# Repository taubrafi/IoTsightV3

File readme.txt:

IoTSights Project:
	
	Case --Solidworks files for enclosure

	CC3200_workspace
		{Lots of files}	--	Lots of test/old stuff
		ProjectV3 		-- 	main project files
			ADXL345		--Code for accelerometer (interrupt never implemented)
			DS2401		--Code for hardware ID chip
			GPS			--Turn GPS on and off
			HMC5883		--Code for compass (with callibration)
			IMU			--Math to calculate orientation angles
			main		--main
			MPL115A2	--Code to read form barometer and convers to kPa
			NetworkFunctions	--HTTP/Server functions
			NMEA				--Code to decode the GPS information
			parameters			--a few defines and paramaters
			pinmux2 (pinmux ignored)	--pin setup
			SD_card						--Code to write to SD card (not implemented fully)
			SimpleLinkFunctions			--Code to connect to Wi-Fi network 

	OLD project files 	-- report/presentation documentation
		
	PCB					-- PCB files (eagle)
	
	IoT_Sight_FULL 		-- Full schematic for PCB (pdf)

To get up and running:
	Install the latest version of CCS according to the TI website for the CC3200.
	Install Uniflash CC3200_sdk and servicepack (all folowing TI directions exactly)
	See:		https://www.youtube.com/watch?v=xbh9I8waq5g
	Or search: 	"SimpleLink Wi-Fi CC3200 Project 0: Code Composer Studio IDE"

You're ready to go

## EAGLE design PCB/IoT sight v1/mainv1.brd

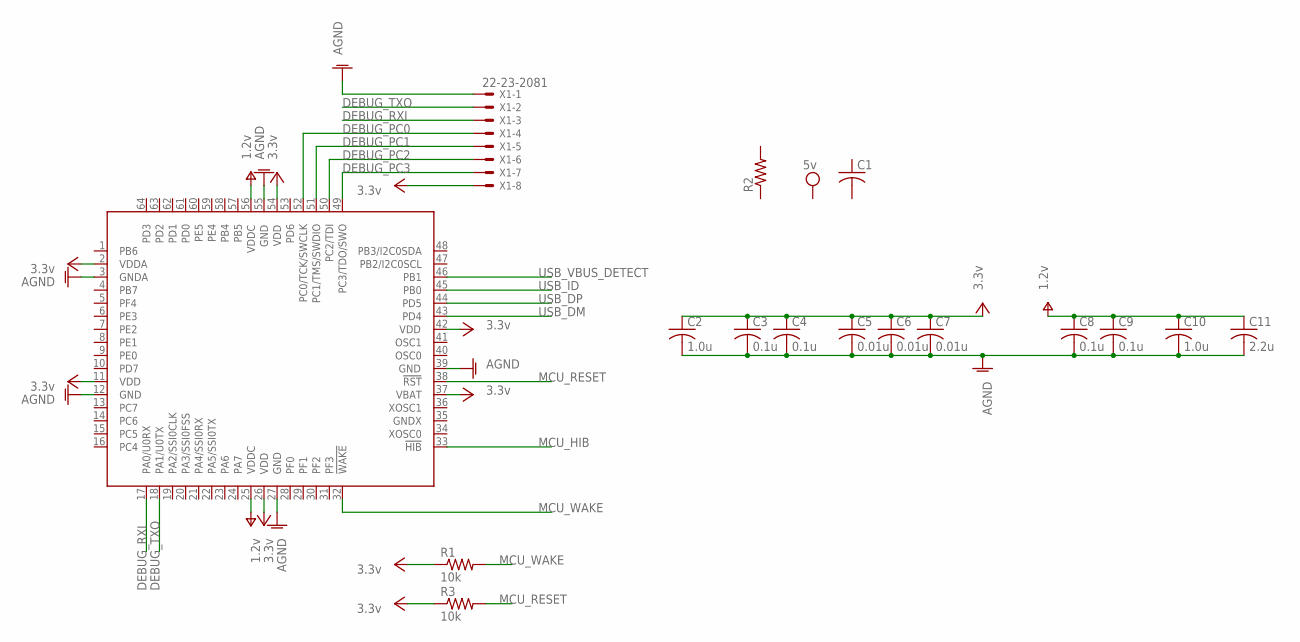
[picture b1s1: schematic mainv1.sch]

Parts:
C1: C-USC0805K; C0805K
C2, C10: 1.0u; C0805K
C3, C4, C8, C9: 0.1u; C0805K
C5, C6, C7: 0.01u; C0805K
C11: 2.2u; C0805K
IC1: TM4C123GH6PMI; PM_S-PQFP-G64
R1, R3: 10k; R0805
R2: R-US_R0805; R0805
X1: 22-23-2081

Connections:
AGND: C2.2, C3.2, C4.2, C5.2, C6.2, C7.2, C8.2, C9.2, C10.2, C11.2, IC1.3 (GNDA), IC1.12 (GND), IC1.27 (GND), IC1.39 (GND), IC1.55 (GND), X1.1
DEBUG_PC0: IC1.52 (PC0/TCK/SWCLK), X1.4
DEBUG_PC1: IC1.51 (PC1/TMS/SWDIO), X1.5
DEBUG_PC2: IC1.50 (PC2/TDI), X1.6
DEBUG_PC3: IC1.49 (PC3/TDO/SWO), X1.7
DEBUG_RXI: IC1.17 (PA0/U0RX), X1.3
DEBUG_TXO: IC1.18 (PA1/U0TX), X1.2
MCU_HIB: IC1.33 (!HIB)
MCU_RESET: IC1.38 (!RST), R3.2
MCU_WAKE: IC1.32 (!WAKE), R1.2
USB_DM: IC1.43 (PD4)
USB_DP: IC1.44 (PD5)
USB_ID: IC1.45 (PB0)
USB_VBUS_DETECT: IC1.46 (PB1)
V+: C8.1, C9.1, C10.1, C11.1, IC1.25 (VDDC), IC1.56 (VDDC)
VCC: C2.1, C3.1, C4.1, C5.1, C6.1, C7.1, IC1.2 (VDDA), IC1.11 (VDD), IC1.26 (VDD), IC1.37 (VBAT), IC1.42 (VDD), IC1.54 (VDD), R1.1, R3.1, X1.8

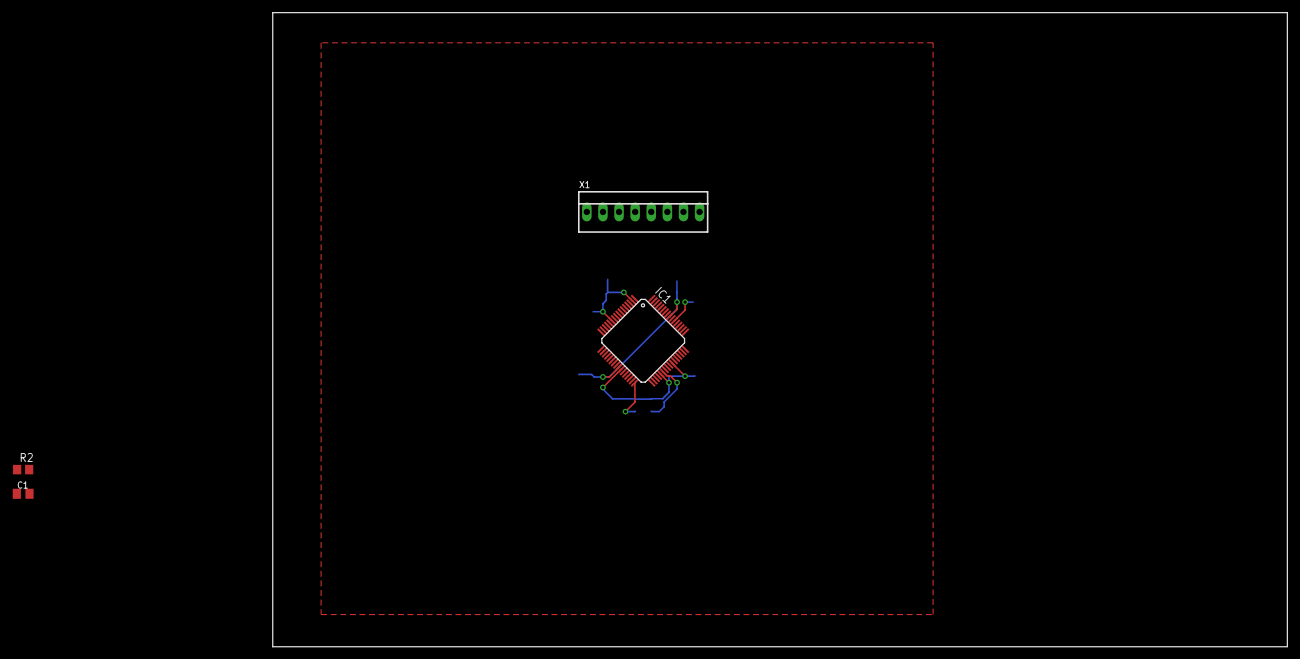
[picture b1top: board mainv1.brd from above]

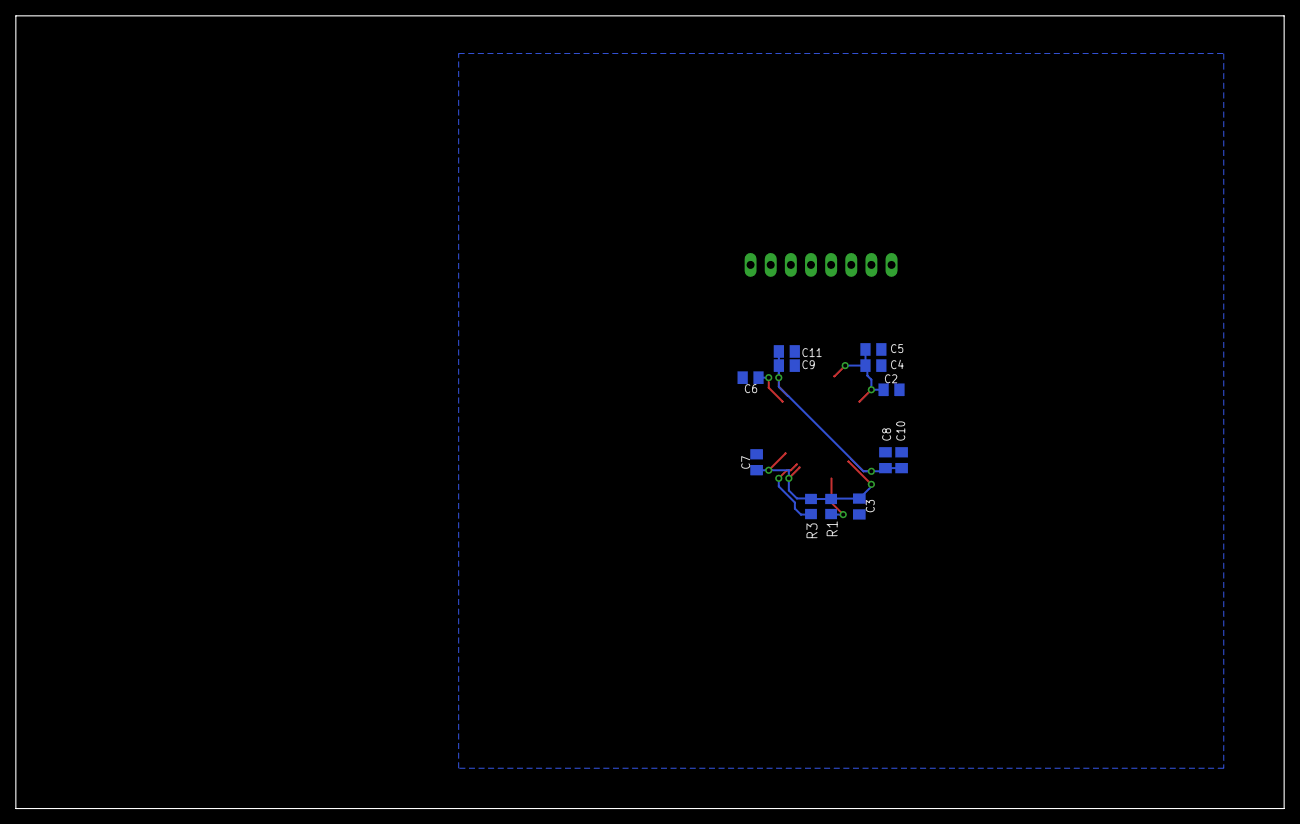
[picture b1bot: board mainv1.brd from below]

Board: 2 copper layers, 160.0 x 100.0 mm, 16 parts (12 on the bottom side), 11 nets.

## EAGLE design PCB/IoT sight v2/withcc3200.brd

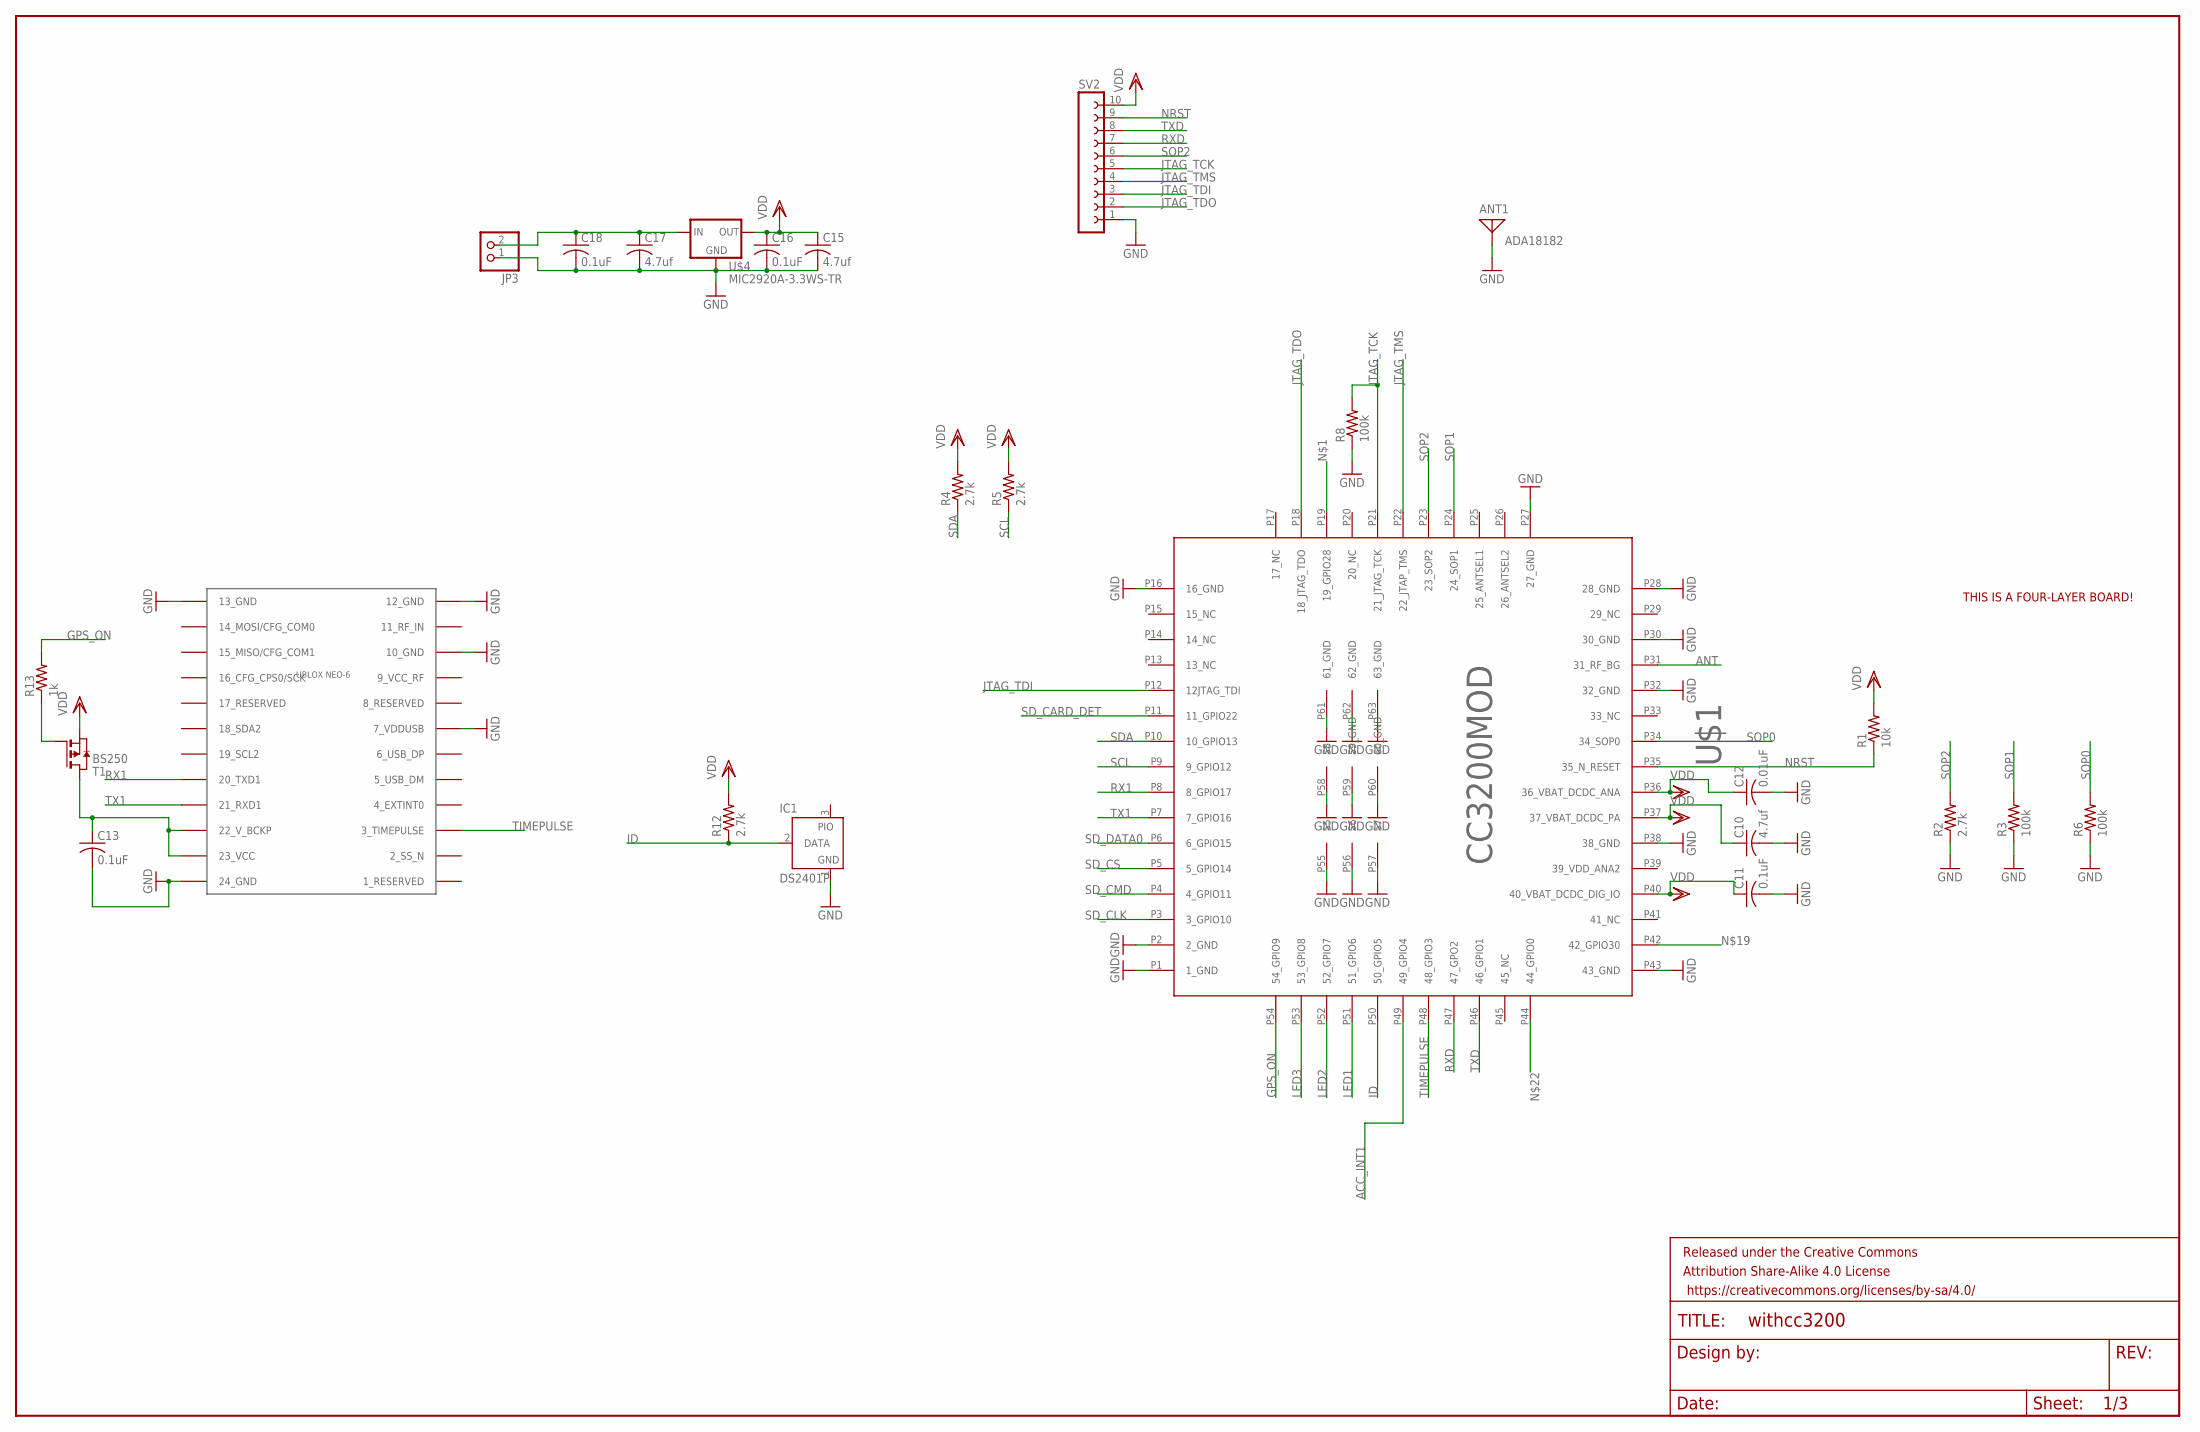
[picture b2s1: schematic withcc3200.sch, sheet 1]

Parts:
ANT1: ADA18182; PAD-01
C10, C15, C17: 4.7uf; C0805K
C11, C13, C16, C18: 0.1uF; C0805K
C12: 0.01uF; C0805K
FRAME1: FRAME-LEDGER; CREATIVE_COMMONS
IC1: DS2401P; TSOC6
JP3: PINHD-1X2; 1X02
R1: 10k; R0603
R2, R4, R5, R12: 2.7k; R0603
R3, R6, R8: 100k; R0603
R13: 1k; R0603
SV2: FE10-1; FE10
T1: BS250; SOT-23
U$1: CC3200MOD
U$2: UBLOX_NEO-7; UBLOX_NEO-6P
U$3: FOUR_LAYER_WARNING
U$4: MIC2920A-3.3WS-TR; SOT223

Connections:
ACC_INT1: U$1.P49 (49_GPIO4); also elsewhere on the board
ANT: U$1.P31 (31_RF_BG)
GND: ANT1.1, C10.2, C11.2, C12.2, C13.2, C15.2, C16.2, C17.2, C18.2, IC1.1 (GND), JP3.1, R2.1, R3.1, R6.1, R8.1, SV2.1, U$1.P1 (1_GND), U$1.P2 (2_GND), U$1.P16 (16_GND), U$1.P27 (27_GND), U$1.P28 (28_GND), U$1.P30 (30_GND), U$1.P32 (32_GND), U$1.P38 (38_GND), U$1.P43 (43_GND), U$1.P55 (55), U$1.P56 (56), U$1.P57 (57), U$1.P58 (58), U$1.P59 (59_GND), U$1.P60 (60_GND), U$1.P61 (61_GND), U$1.P62 (62_GND), U$1.P63 (63_GND), U$2.7_VDDUSB, U$2.10_GND, U$2.12_GND, U$2.13_GND, U$2.24_GND, U$4.2 (GND); also elsewhere on the board
GPS_ON: R13.2, U$1.P54 (54_GPIO9)
ID: IC1.2 (DATA), R12.1, U$1.P50 (50_GPIO5)
JTAG_TCK: R8.2, SV2.5, U$1.P21 (21_JTAG_TCK)
JTAG_TDI: SV2.3, U$1.P12 (12JTAG_TDI)
JTAG_TDO: SV2.2, U$1.P18 (18_JTAG_TDO)
JTAG_TMS: SV2.4, U$1.P22 (22_JTAP_TMS)
LED1: U$1.P51 (51_GPIO6); also elsewhere on the board
LED2: U$1.P52 (52_GPIO7); also elsewhere on the board
LED3: U$1.P53 (53_GPIO8); also elsewhere on the board
unnamed: C17.1, C18.1, JP3.2, U$4.1 (IN)
unnamed: C13.1, T1.1 (D), U$2.22_V_BCKP, U$2.23_VCC
unnamed: R13.1, T1.3 (G)
NRST: R1.1, SV2.9, U$1.P35 (35_N_RESET)
RX1: U$1.P8 (8_GPIO17), U$2.20_TXD1
RXD: SV2.7, U$1.P47 (47_GPO2)
SCL: R5.1, U$1.P9 (9_GPIO12); also elsewhere on the board
SDA: R4.1, U$1.P10 (10_GPIO13); also elsewhere on the board
SD_CARD_DET: U$1.P11 (11_GPIO22); also elsewhere on the board
SD_CLK: U$1.P3 (3_GPIO10); also elsewhere on the board
SD_CMD: U$1.P4 (4_GPIO11); also elsewhere on the board
SD_CS: U$1.P5 (5_GPIO14); also elsewhere on the board
SD_DATA0: U$1.P6 (6_GPIO15); also elsewhere on the board
SOP0: R6.2, U$1.P34 (34_SOP0)
SOP1: R3.2, U$1.P24 (24_SOP1)
SOP2: R2.2, SV2.6, U$1.P23 (23_SOP2)
TIMEPULSE: U$1.P48 (48_GPIO3), U$2.3_TIMEPULSE
TX1: U$1.P7 (7_GPIO16), U$2.21_RXD1
TXD: SV2.8, U$1.P46 (46_GPIO1)
VDD: C10.1, C11.1, C12.1, C15.1, C16.1, R1.2, R4.2, R5.2, R12.2, SV2.10, T1.2 (S), U$1.P36 (36_VBAT_DCDC_ANA), U$1.P37 (37_VBAT_DCDC_PA), U$1.P40 (40_VBAT_DCDC_DIG_IO), U$4.3 (OUT); also elsewhere on the board

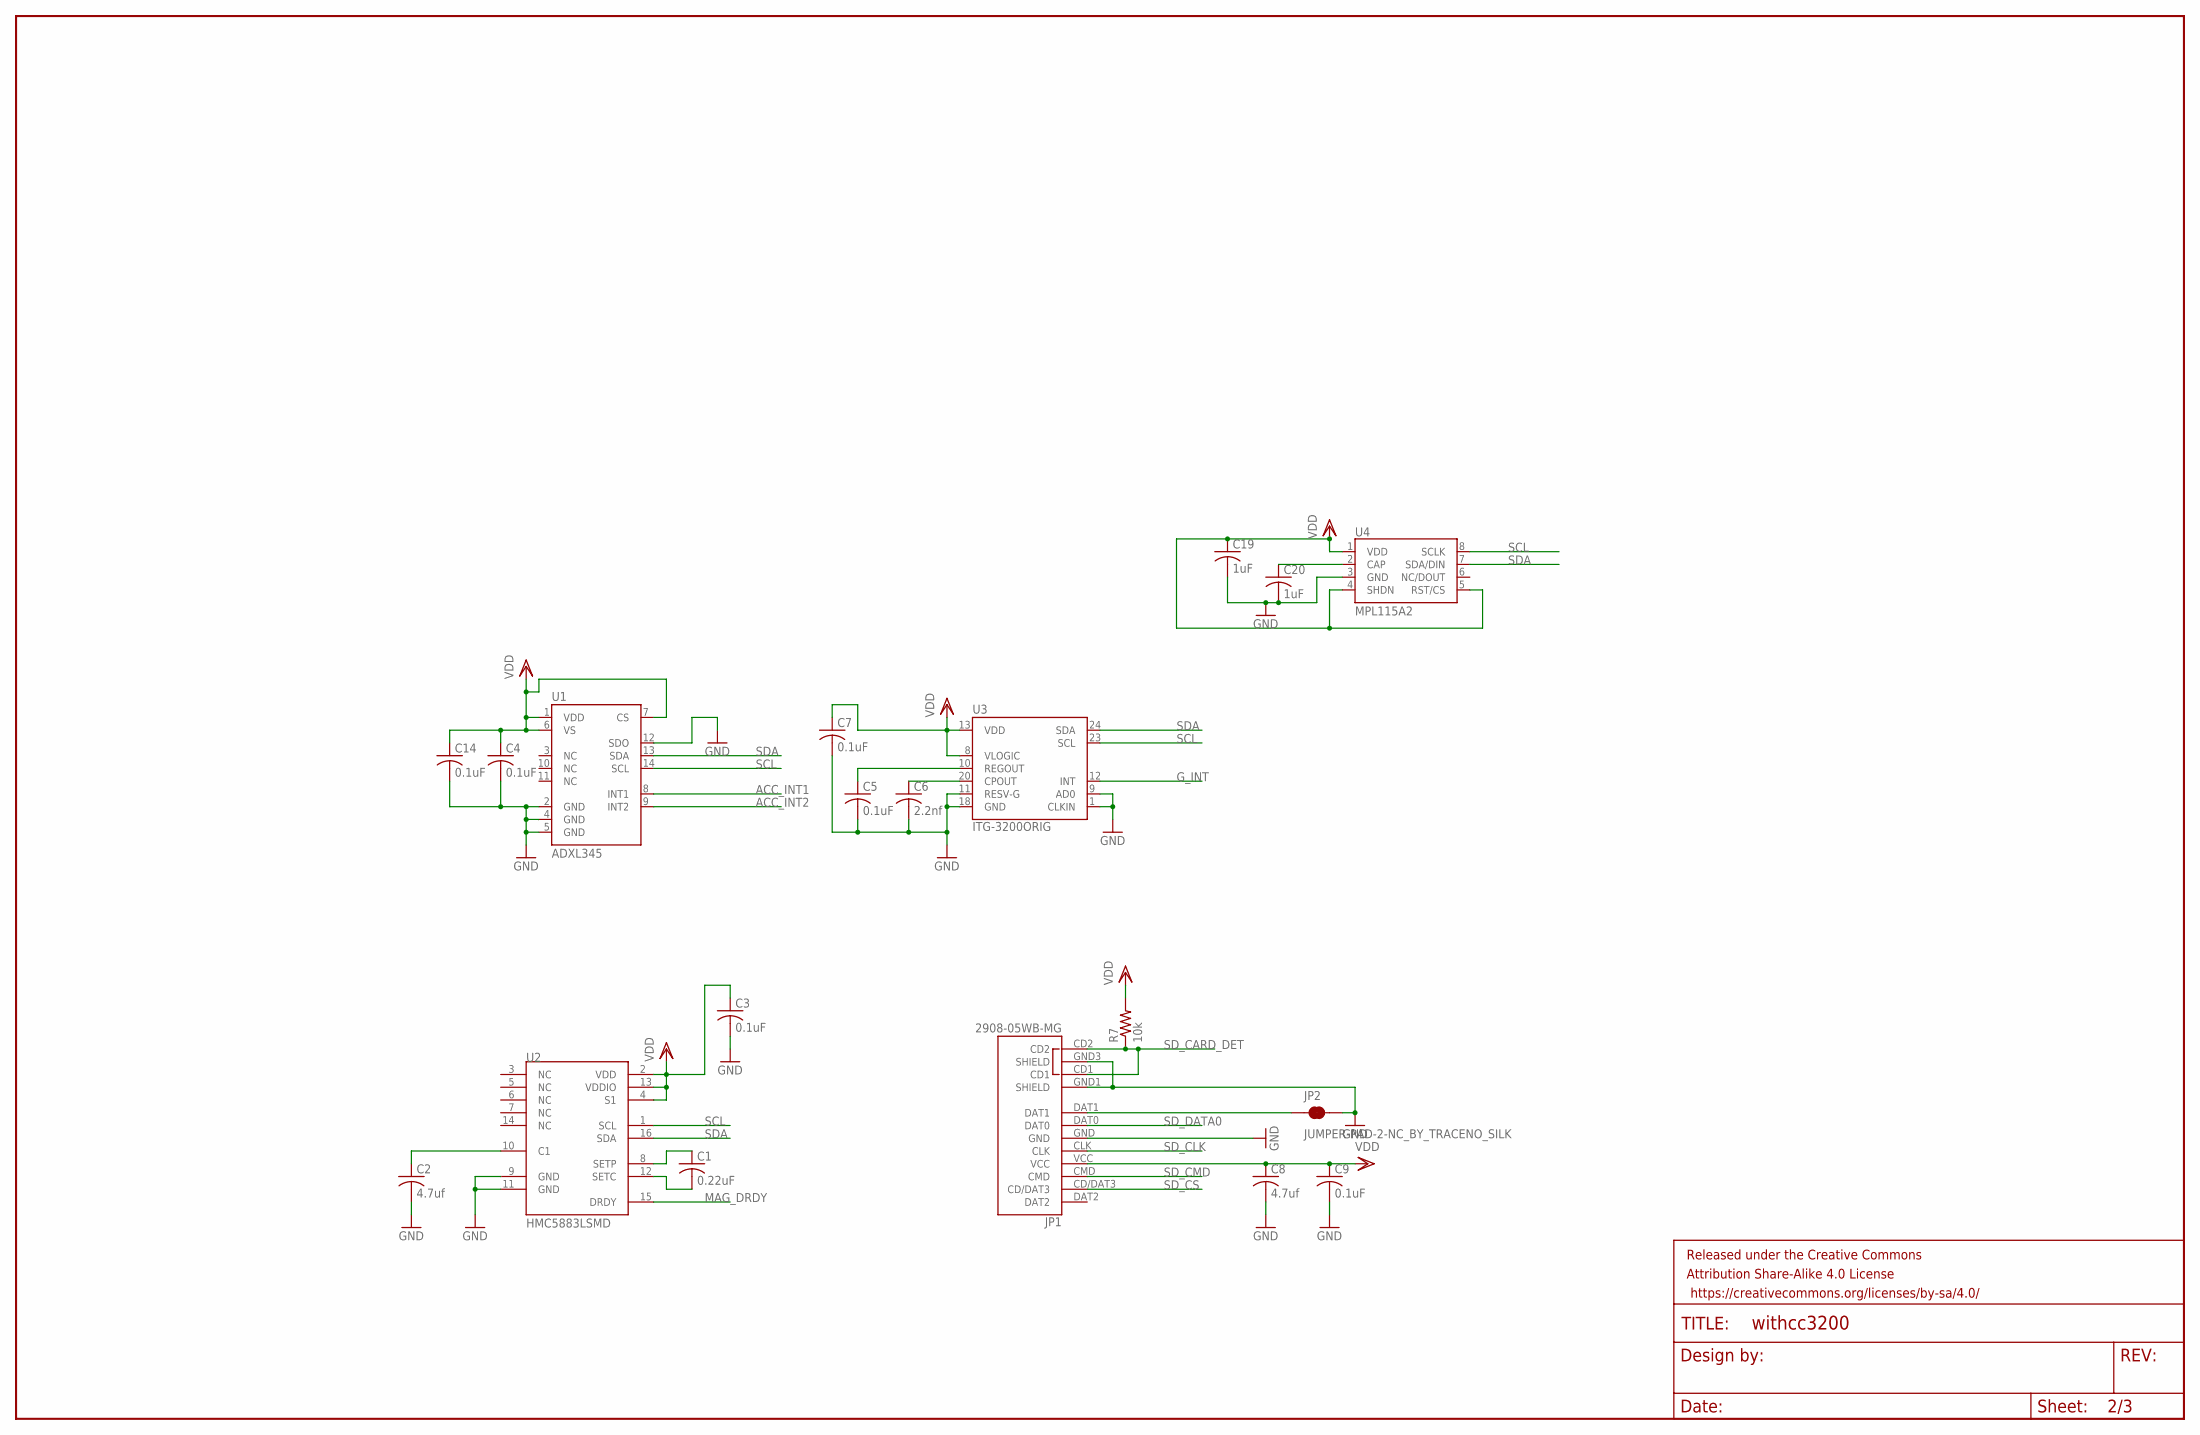
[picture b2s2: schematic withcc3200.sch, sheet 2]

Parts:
C1: 0.22uF; C0805K
C2, C8: 4.7uf; C0805K
C3, C4, C5, C7, C9, C14: 0.1uF; C0805K
C6: 2.2nf; C0805K
C19, C20: 1uF; C0805K
FRAME2: FRAME-LEDGER; CREATIVE_COMMONS
JP1: 2908-05WB-MG; MICRO-SD-SOCKET-SDIO
JP2: JUMPER-PAD-2-NC_BY_TRACENO_SILK; PAD-JUMPER-2-NC_BY_TRACE_NO_SILK
R7: 10k; R0603
U1: ADXL345; LGA14
U2: HMC5883LSMD; 16LPCC
U3: ITG-3200ORIG; QFN-24
U4: MPL115A2; LGA8

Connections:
ACC_INT1: U1.8 (INT1); also elsewhere on the board
ACC_INT2: U1.9 (INT2)
GND: C2.2, C3.2, C4.2, C5.2, C6.2, C7.2, C8.2, C9.2, C14.2, C19.2, C20.2, JP1.GND, JP1.GND1 (SHIELD), JP1.GND3 (SHIELD), JP2.2, U1.2 (GND), U1.4 (GND), U1.5 (GND), U1.12 (SDO), U2.9 (GND), U2.11 (GND), U3.1 (CLKIN), U3.9 (AD0), U3.11 (RESV-G), U3.18 (GND), U4.3 (GND); also elsewhere on the board
G_INT: U3.12 (INT)
MAG_DRDY: U2.15 (DRDY)
unnamed: JP1.DAT1, JP2.1
unnamed: C1.2, U2.12 (SETC)
unnamed: C1.1, U2.8 (SETP)
unnamed: C2.1, U2.10 (C1)
unnamed: C5.1, U3.10 (REGOUT)
unnamed: C6.1, U3.20 (CPOUT)
unnamed: C20.1, U4.2 (CAP)
SCL: U1.14 (SCL), U2.1 (SCL), U3.23 (SCL), U4.8 (SCLK); also elsewhere on the board
SDA: U1.13 (SDA), U2.16 (SDA), U3.24 (SDA), U4.7 (SDA/DIN); also elsewhere on the board
SD_CARD_DET: JP1.CD1, JP1.CD2, R7.1; also elsewhere on the board
SD_CLK: JP1.CLK; also elsewhere on the board
SD_CMD: JP1.CMD; also elsewhere on the board
SD_CS: JP1.CD/DAT3; also elsewhere on the board
SD_DATA0: JP1.DAT0; also elsewhere on the board
VDD: C3.1, C4.1, C7.1, C8.1, C9.1, C14.1, C19.1, JP1.VCC, R7.2, U1.1 (VDD), U1.6 (VS), U1.7 (CS), U2.2 (VDD), U2.4 (S1), U2.13 (VDDIO), U3.8 (VLOGIC), U3.13 (VDD), U4.1 (VDD), U4.4 (SHDN), U4.5 (RST/CS); also elsewhere on the board

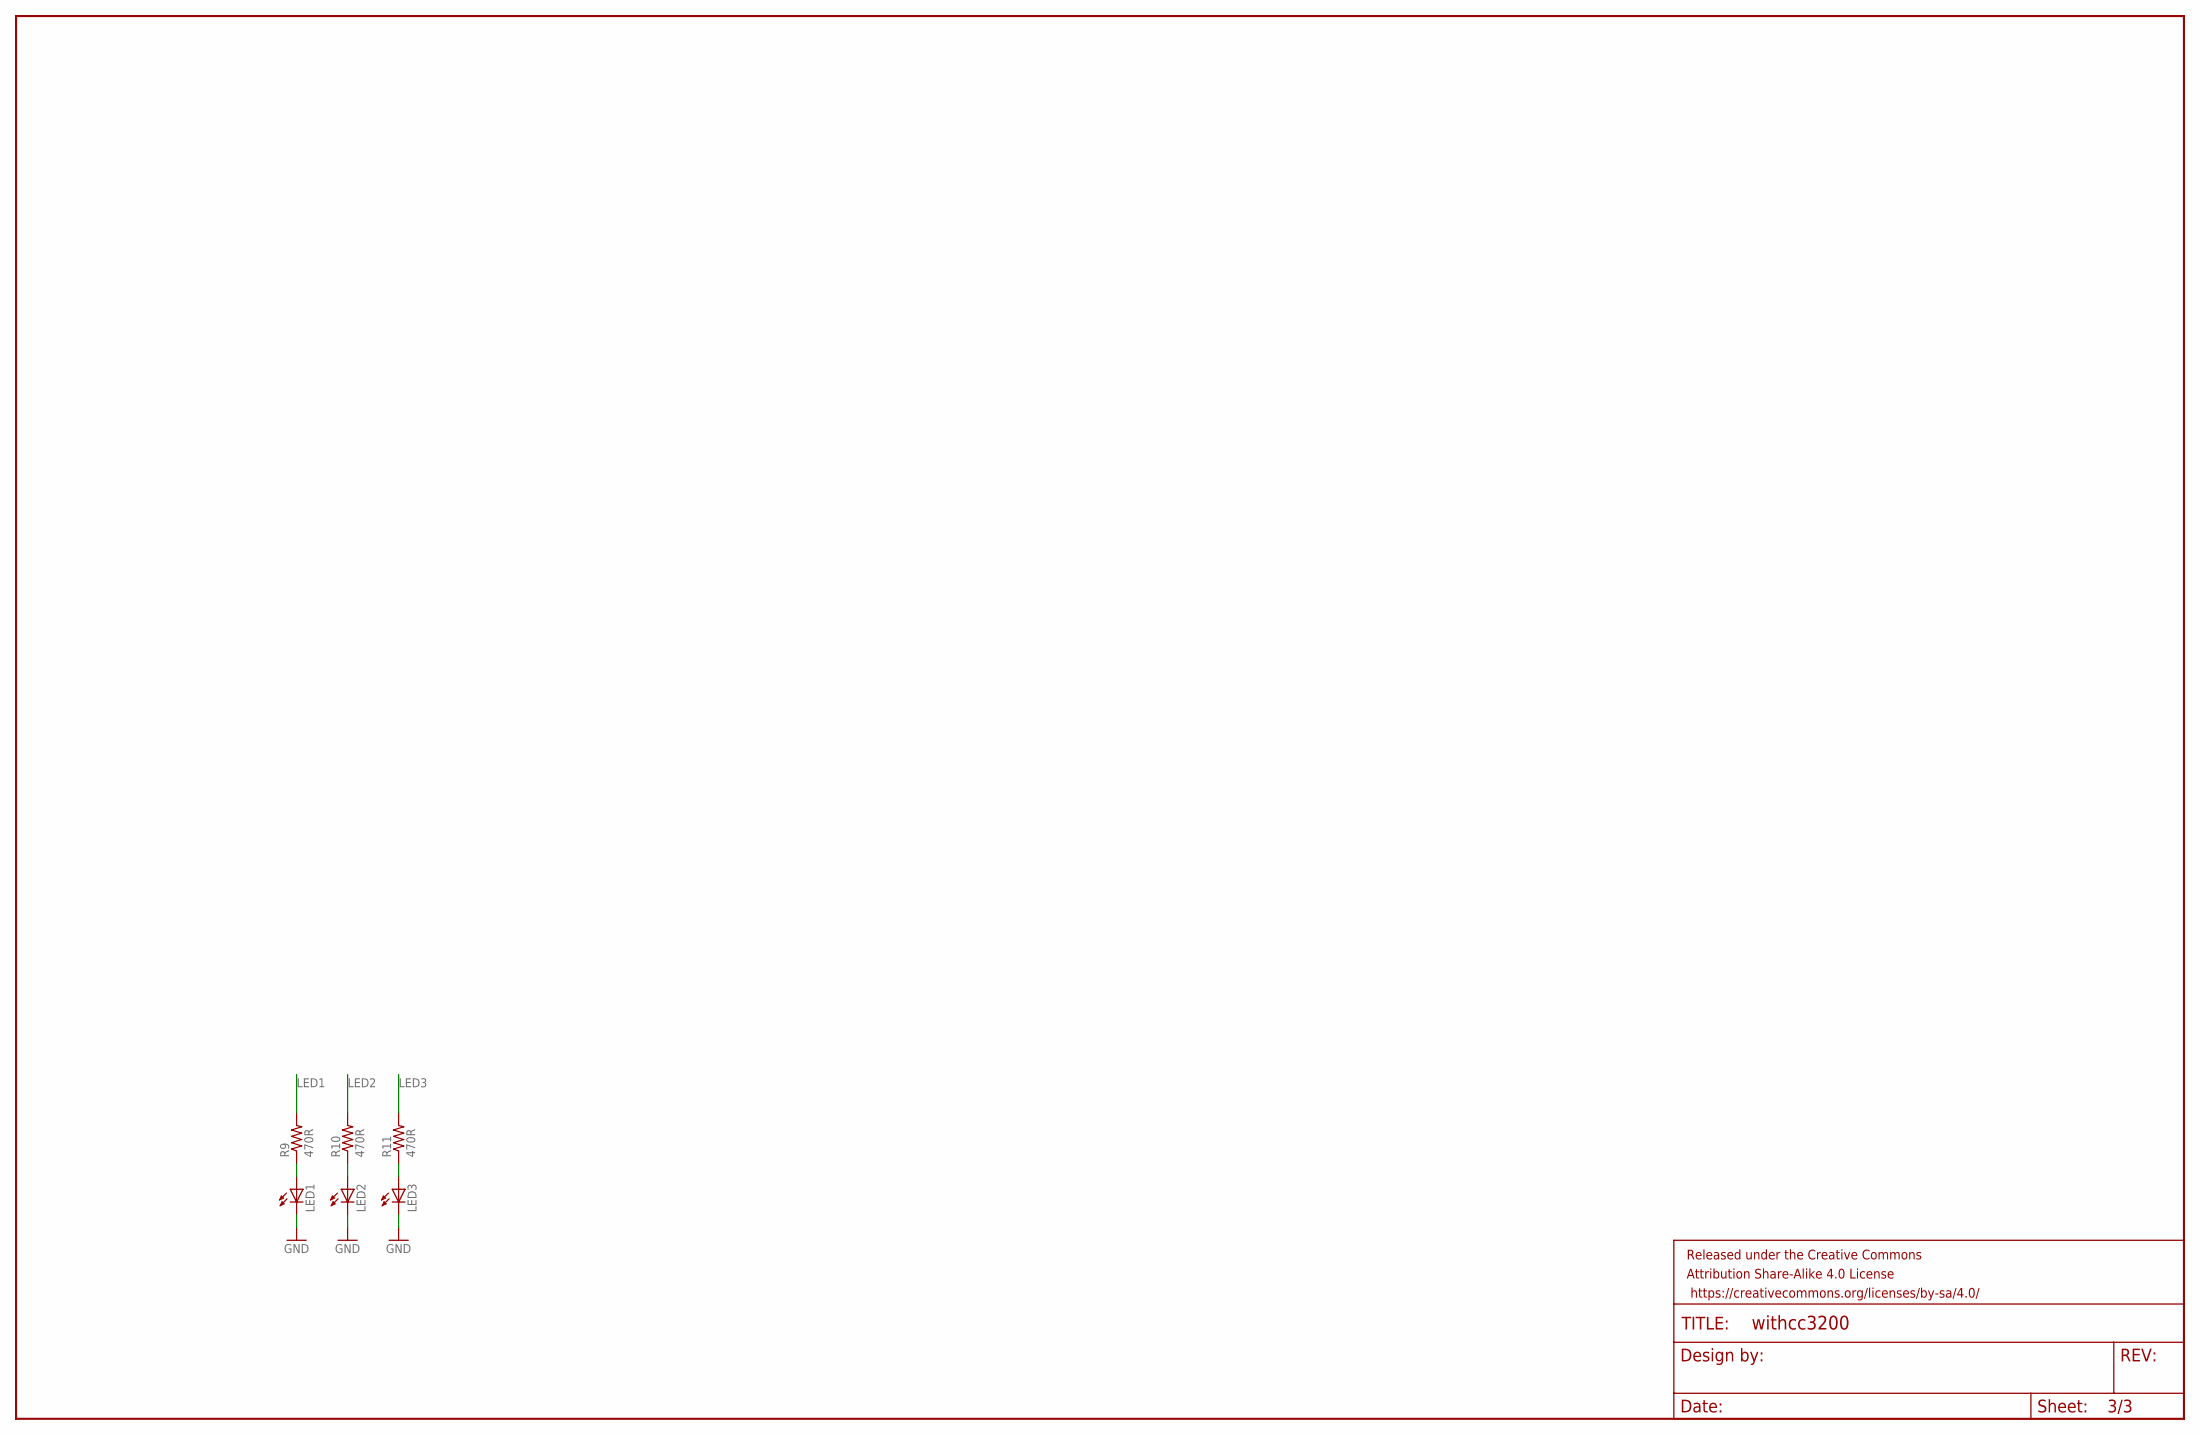
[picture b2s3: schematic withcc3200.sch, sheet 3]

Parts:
FRAME3: FRAME-LEDGER; CREATIVE_COMMONS
LED1, LED2, LED3: LEDCHIPLED_0805; CHIPLED_0805
R9, R10, R11: 470R; R0603

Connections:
GND: LED1.C, LED2.C, LED3.C; also elsewhere on the board
LED1: R9.2; also elsewhere on the board
LED2: R10.2; also elsewhere on the board
LED3: R11.2; also elsewhere on the board
unnamed: LED1.A, R9.1
unnamed: LED2.A, R10.1
unnamed: LED3.A, R11.1

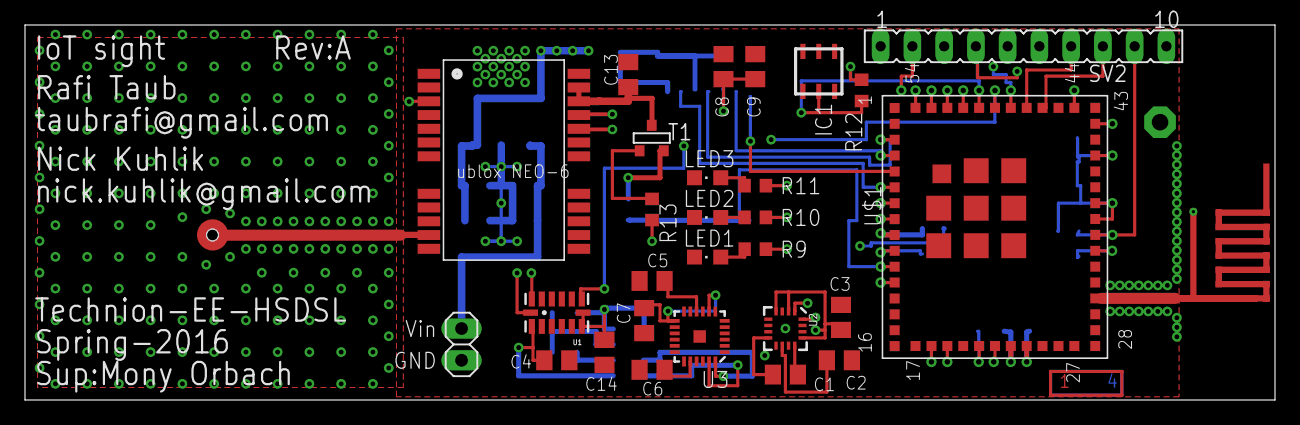
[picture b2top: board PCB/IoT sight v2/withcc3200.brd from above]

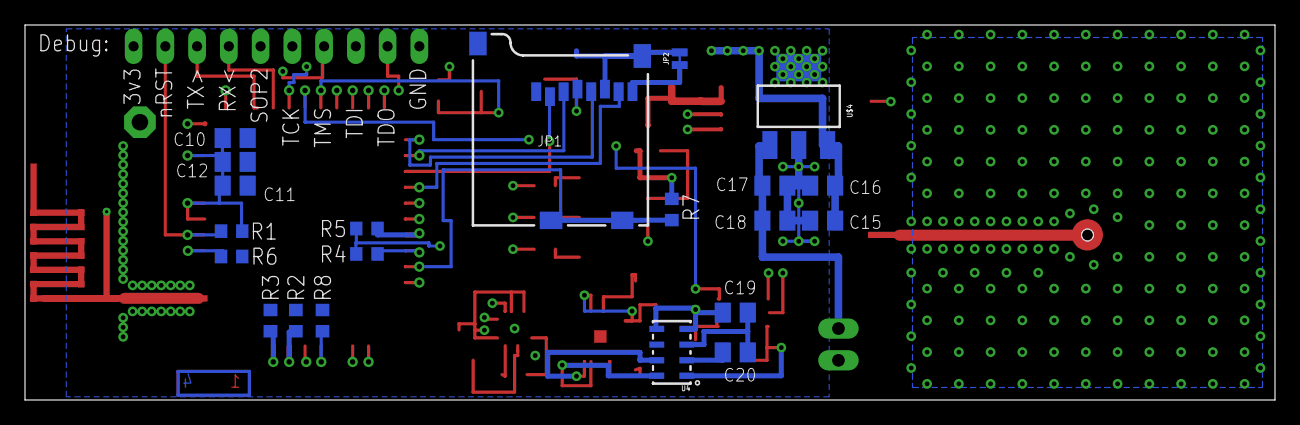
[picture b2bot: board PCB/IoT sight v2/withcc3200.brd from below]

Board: 4 copper layers, 100.0 x 30.0 mm, 54 parts (21 on the bottom side), 41 nets.

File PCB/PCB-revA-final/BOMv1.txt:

Value/part number	Qty		Package					Notes						URL
ADA18182			1		GPS_Antenna											http://il.farnell.com/adactus/ada-18182/antenna-gps-patch-2-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
cap 0.22uF			1		C-0805												***generic 0805-0.22uF cap***	
cap 4.7uf			5		C-0805												***generic 0805-4.7uF cap***	
cap 0.1uF			10		C-0805												***generic 0805-0.1uF cap***	
cap 2.2nf			1		C-0805												***generic 0805-2.2nF cap***	
cap 0.01uF			1		C-0805												***generic 0805-0.01uF cap***	
cap 1uF				2		C-0805												***generic 0805-1.0uF cap***	
DS2401P				1		TSOC6					DS2401P+					http://il.farnell.com/maxim-integrated-products/ds2401p/sili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
47352-1001			1		MICRO-SD-SOCKET-SDIO								http://il.farnell.com/molex/47352-1001/connector-micro-sd-8p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
Generic 0805 LED	3		CHIPLED_0805										***generic 0805 LED***		
res 10k				2		R-0603												***generic 0603-10k res***	
res 2.7k			5		R-0603												***generic 0603-2.7k res***	
res 100k			3		R-0603												***generic 0603-100k res***	
res 470R			3		R-0603												***generic 0603-470R res***	
BS250				1		SOT-23					May be called TP0610T		http://il.farnell.com/diodes-inc/bs250fta/mosfet-p-ch-45v-0-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
CC3200MOD			1		CC3200MOD				Make sure suffix MOD !		http://www.ti.com/product/cc3200mod/samplebuy
UBLOX_NEO-6M		1		UBLOX_NEO-6M										http://www.ebay.com/itm/NEO-6M-0-001-NEO-6M-U-blox-GPS-Posit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
MIC2920A-3.3WS-TR	1		SOT223												http://il.farnell.com/microchip/mic2920a-3-3ws-tr/ldo-reg-26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
ADXL345				1		LGA14												http://il.farnell.com/analog-devices/adxl345bccz/ic-accelero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
HMC5883L			1		16LPCC					Make sure suffix L !		http://il.farnell.com/honeywell/hmc5883l-tr/ic-digital-compa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
ITG-3200			1		QFN-24					***Only buy 2or3 total***	http://il.farnell.com/invensense/itg-3200/ic-gyro-tri-axis-2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
MPL115A2			1		LGA8					Make sure suffix A2 !		http://il.farnell.com/nxp/mpl115a2/mini-i2c-digital-baromete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

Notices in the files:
parts and their libraries:
SparkFun-Sensors: Licensing: Creative Commons ShareAlike 4.0 International - https://creativecommons.org/licenses/by-sa/4.0
SparkFun-Aesthetics: Released under the Creative Commons Attribution Share-Alike 4.0 License
SparkFun-Aesthetics: https://creativecommons.org/licenses/by-sa/4.0
